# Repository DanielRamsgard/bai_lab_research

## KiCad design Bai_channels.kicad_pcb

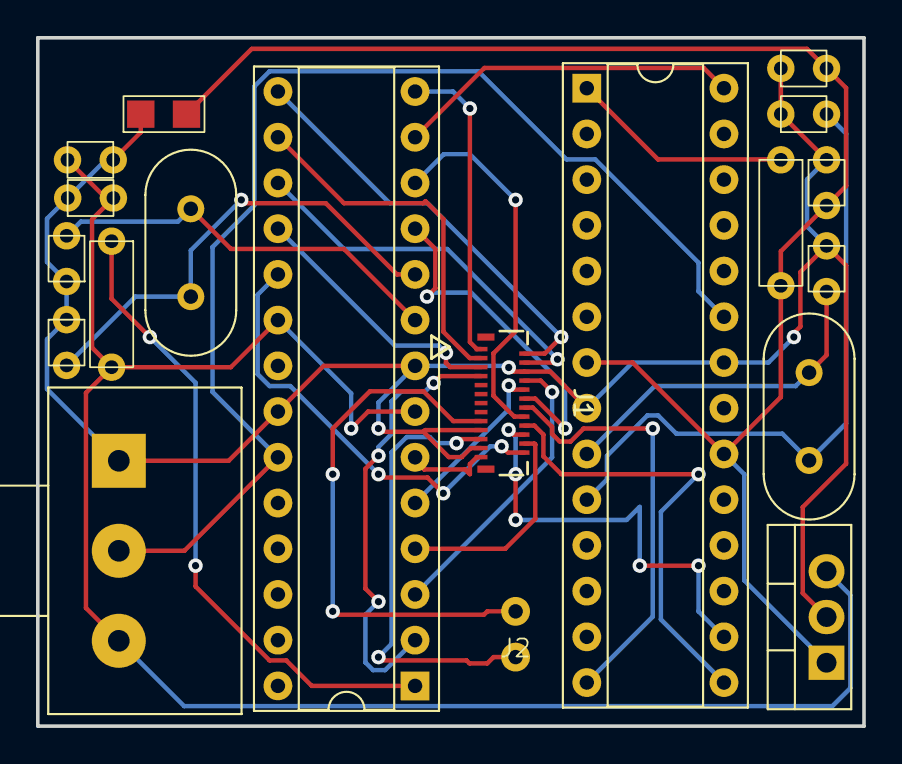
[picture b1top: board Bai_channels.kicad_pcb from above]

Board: 2 copper layers, 45.9 x 38.2 mm, 19 parts (0 on the bottom side), 29 nets.

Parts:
16MHz1, 16MHz2: Crystal; Crystal_HC49-4H_Vertical
C1, C2: 1µF; capacitor
C3, C4: 10µF; capacitor
C5, C6, C7, C8: 22pF; capacitor
J1: 5020782510; CON_5020782510
J2: Conn_01x02_Pin; pinHeader
R1, R2: 10kR; R
RV1: R_Potentiometer; Potentiometer_Alps_RK163_Single_Horizontal
U1: power
U2: LM7805_TO220; TO-220-3_Vertical
U3, U4: ATmega328-P; DIP-28_W7.62mm_Socket

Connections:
unnamed: J1.17, J2.1
unnamed: J1.21, J2.2
unnamed: C1.2, C2.2, C3.2, C4.2, C5.2, C6.2, C7.2, C8.2, J1.6, J1.19, J1.23, RV1.1, U1.2 (GND), U2.2 (GND), U3.8 (GND), U3.22 (GND), U4.8 (GND), U4.22 (GND)
unnamed: C1.1, C4.1, R2.2, U1.1 (VCC), U2.1 (VI), U4.7 (VCC), U4.20 (AVCC)
unnamed: C2.1, C3.1, R1.2, RV1.3, U2.3 (VO), U3.7 (VCC), U3.20 (AVCC)
unnamed: J1.1, U3.14 (PB0)
unnamed: J1.2, U3.15 (PB1)
unnamed: J1.3, U3.16 (PB2)
unnamed: J1.4, U3.17 (PB3)
unnamed: J1.5, U3.18 (PB4)
unnamed: J1.24, U3.19 (PB5)
unnamed: RV1.2, U3.23 (PC0), U4.23 (PC0)
unnamed: J1.7, U3.2 (PD0)
unnamed: J1.8, U3.3 (PD1)
unnamed: J1.22, U3.4 (PD2)
unnamed: J1.10, U3.5 (PD3)
unnamed: J1.25, U3.6 (PD4)
unnamed: J1.12, U3.11 (PD5)
unnamed: J1.16, U3.12 (PD6)
unnamed: U3.13 (PD7), U4.28 (PC5)
unnamed: 16MHz1.1, C6.1, U3.9 (XTAL1/PB6)
unnamed: 16MHz1.2, C5.1, U3.10 (XTAL2/PB7)
unnamed: R1.1, U3.1 (~RESET/PC6)
unnamed: J1.14, U4.14 (PB0)
unnamed: J1.18, U4.15 (PB1)
unnamed: J1.20, U4.16 (PB2)
unnamed: 16MHz2.1, C8.1, U4.9 (XTAL1/PB6)
unnamed: 16MHz2.2, C7.1, U4.10 (XTAL2/PB7)
unnamed: R2.1, U4.1 (~RESET/PC6)

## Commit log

2024-01-19 34 to 32 channels change
2024-01-26 vibration motor footprint
2024-01-26 save
2024-01-26 led footprints
2024-01-26 updated PCB editor
2024-01-28 new desing to incorporate FPC Cable
2024-01-28 custom cable footprint
2024-01-29 Official FPC
2024-02-04 traces
2024-02-05 two-layer routing complete pray for 3-layer possibility
2024-02-05 board complete with four layers
2024-02-09 adding STM design and bioelectronics dir
2024-02-09 16 channel
2024-02-09 work
2024-02-09 more routing
2024-02-09 final track
2024-02-09 design complete
2024-03-11 final design
2024-03-25 finished design
2024-03-25 added bai_emap
